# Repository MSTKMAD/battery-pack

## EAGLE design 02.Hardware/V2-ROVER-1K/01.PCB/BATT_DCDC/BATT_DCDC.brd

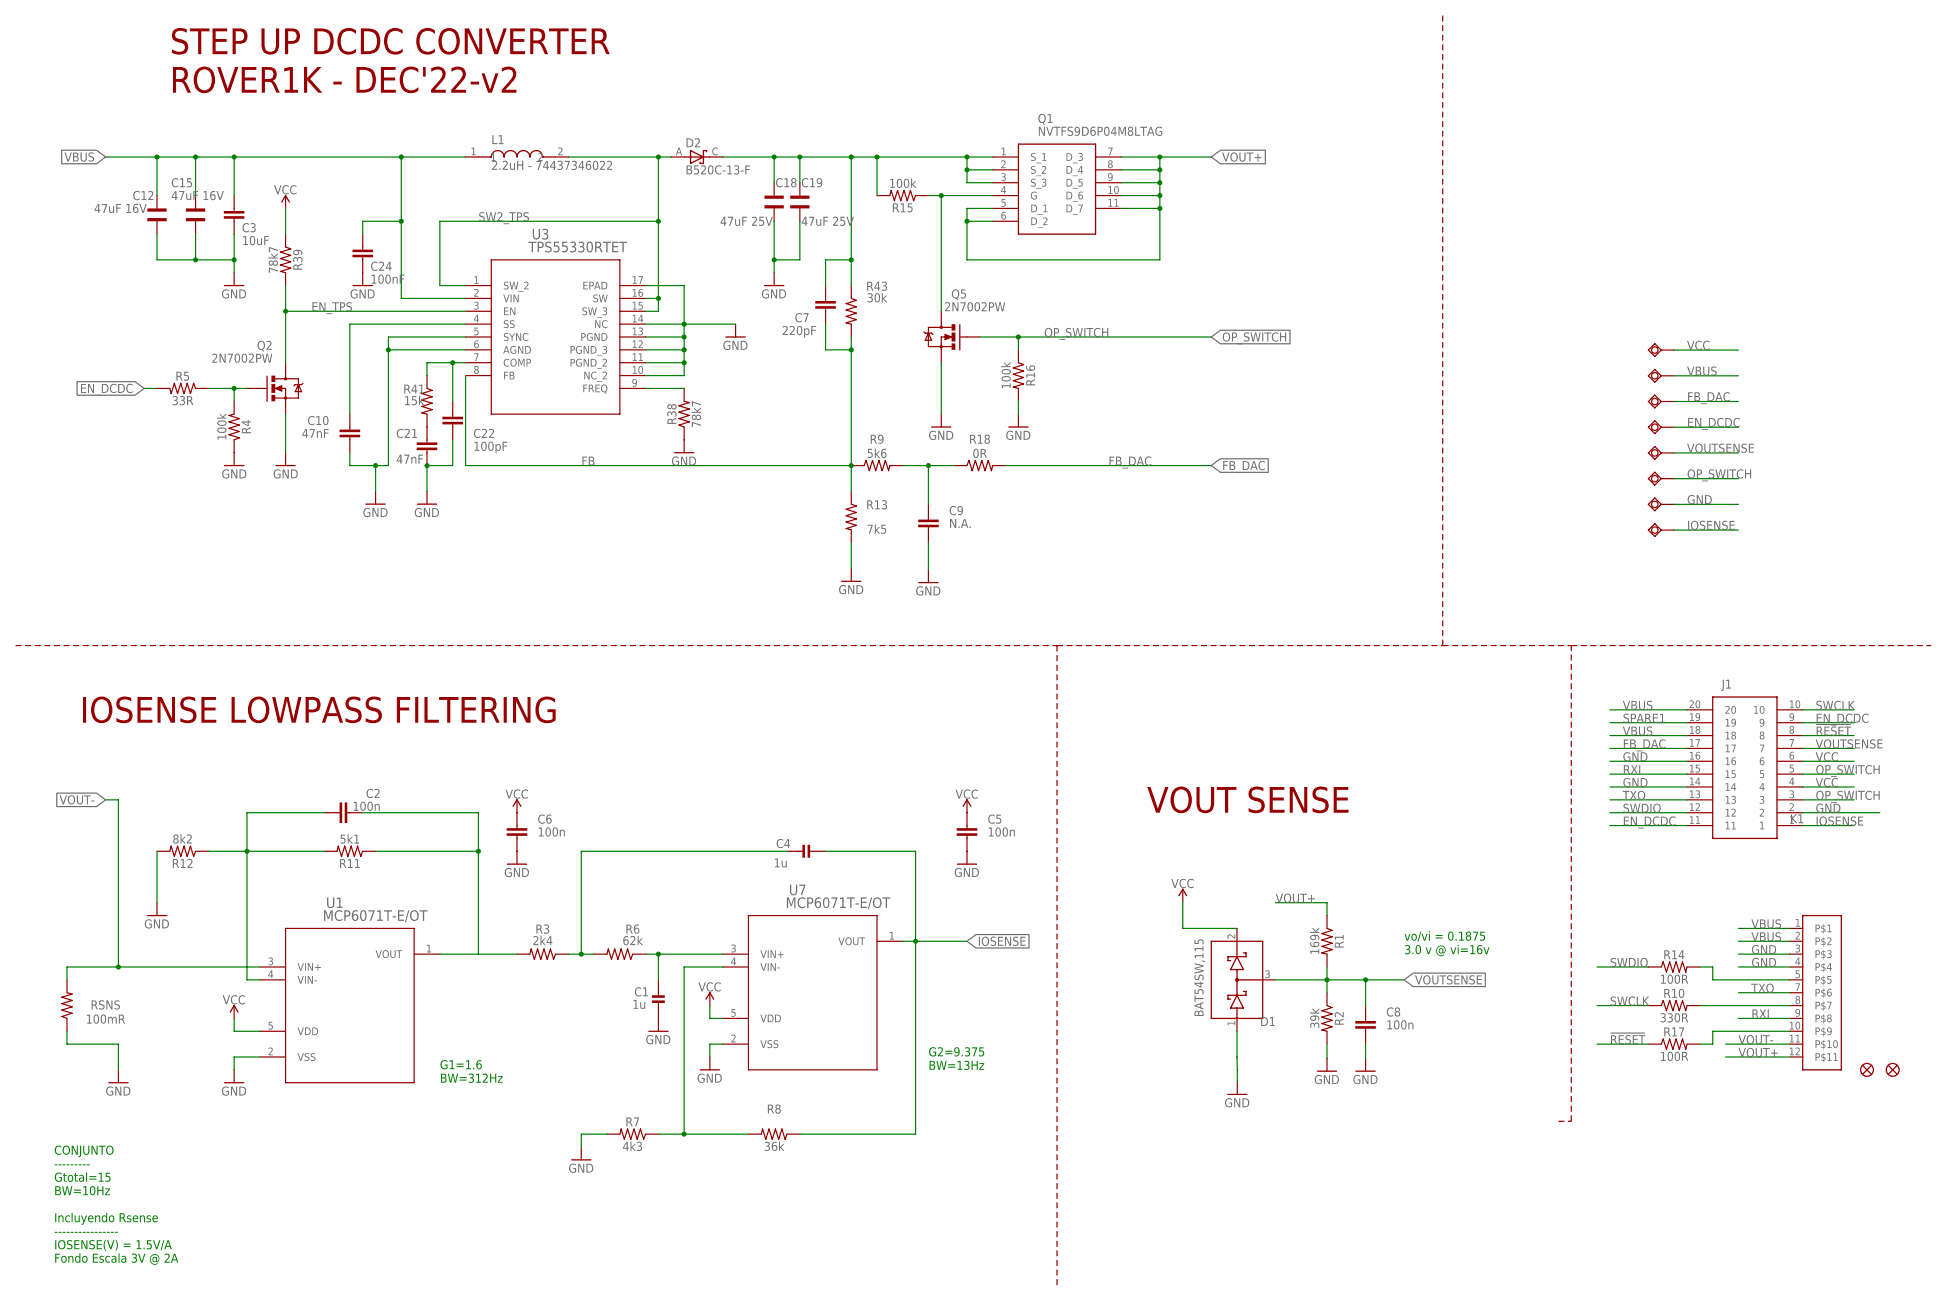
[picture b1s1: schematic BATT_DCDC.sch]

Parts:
C1, C4: 1u; 0603-NO
C2, C5, C6, C8: 100n; 0603
C3: 10uF; 0805
C7: 220pF; 0603
C9: N.A.; 0603
C10, C21: 47nF; 0603
C12, C15: 47uF 16V; WCAP-CSGP_1210
C18, C19: 47uF 25V; WCAP-CSGP_1210
C22: 100pF; 0603
C24: 100nF; 0603
D1: BAT54SW,115; SOT65P210X110-3N
D2: B520C-13-F; DIOM7959X250N
EN_DCDC: TESTPAD_TPSQB1,27; TESTPAD_B1,27
FB_DAC: TESTPAD_TPSQB1,27; TESTPAD_B1,27
GND: TESTPAD_TPSQB1,27; TESTPAD_B1,27
IOSENSE: TESTPAD_TPSQB1,27; TESTPAD_B1,27
J1: DF40C-20DP-0.4V_51_; DF40C-20DPA
K1: FLEX11
L1: 2.2uH - 74437346022; INDM7366X500
OP_SWITCH: TESTPAD_TPSQB1,27; TESTPAD_B1,27
Q1: NVTFS9D6P04M8LTAG; NVTFS5124PLTWG
Q2, Q5: 2N7002PW; SOT323
R1: 169k; 0402
R2: 39k; 0402
R3: 2k4; 0603
R4, R15, R16: 100k; 0402
R5: 33R; 0402
R6: 62k; 0603
R7: 4k3; 0603
R8: 36k; 0603
R9: 5k6; 0402
R10: 330R; 0402
R11: 5k1; 0402
R12: 8k2; 0402
R13: 7k5; 0402
R14, R17: 100R; 0402
R18: 0R; 0402
R38, R39: 78k7; 0402
R41: 15k; 0402
R43: 30k; 0402
RSNS: 100mR; 1206
U1, U7: MCP6071T-E/OT; SOT-23-5_MC_MCH
U3: TPS55330RTET; RTE16_1P66X1P66_TEX
U$1, U$2: FIDUCIAL""; FIDUCIAL_1MM
VBUS: TESTPAD_TPSQB1,27; TESTPAD_B1,27
VCC: TESTPAD_TPSQB1,27; TESTPAD_B1,27
VOUTSENSE: TESTPAD_TPSQB1,27; TESTPAD_B1,27

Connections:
!RESET: J1.8, R17.1
COMP_TPS: C22.2, R41.1, U3.7 (COMP)
EN_DCDC: EN_DCDC.TP, J1.9, J1.11, R5.2
EN_TPS: Q2.3 (D), R39.2, U3.3 (EN)
FB: C7.1, R9.1, R13.1, R43.2, U3.8 (FB)
FB_DAC: FB_DAC.TP, J1.17, R18.2
FREQ_TPS: R38.2, U3.9 (FREQ)
GND: C1.2, C3.1, C5.2, C6.2, C8.2, C9.2, C10.2, C12.1, C15.1, C18.1, C19.1, C21.1, C22.1, C24.1, D1.1 (A), GND.TP, J1.2, J1.14, J1.16, K1.3, K1.4, Q2.2 (S), Q5.2 (S), R2.2, R4.1, R7.2, R12.2, R13.2, R16.2, R38.1, RSNS.1, U1.2 (VSS), U3.5 (SYNC), U3.6 (AGND), U3.10 (NC_2), U3.11 (PGND_2), U3.12 (PGND_3), U3.13 (PGND), U3.14 (NC), U3.17 (EPAD), U7.2 (VSS)
IOSENSE: C4.2, IOSENSE.TP, J1.1, R8.1, U7.1 (VOUT)
ISENSE_RAW: C2.1, R3.2, R11.1, U1.1 (VOUT)
unnamed: C2.2, R11.2, R12.1, U1.4 (VIN-)
unnamed: R7.1, R8.2, U7.4 (VIN-)
unnamed: C4.1, R3.1, R6.2
unnamed: Q2.1 (G), R4.2, R5.1
unnamed: C1.1, R6.1, U7.3 (VIN+)
unnamed: K1.8, R10.2
unnamed: Q1.4 (G), Q5.3 (D), R15.1
unnamed: K1.10, R17.2
unnamed: K1.5, R14.2
unnamed: C9.1, R9.2, R18.1
unnamed: C10.1, U3.4 (SS)
unnamed: C21.2, R41.2
OP_SWITCH: J1.3, J1.5, OP_SWITCH.TP, Q5.1 (G), R16.1
RXI: J1.15, K1.9
SPARE1: J1.19
SW2_TPS: D2.A, L1.2, U3.1 (SW_2), U3.15 (SW_3), U3.16 (SW)
SWCLK: J1.10, R10.1
SWDIO: J1.12, R14.1
TXO: J1.13, K1.7
VBUS: C3.2, C12.2, C15.2, C24.2, J1.18, J1.20, K1.1, K1.2, L1.1, U3.2 (VIN), VBUS.TP
VCC: C5.1, C6.1, D1.2 (C), J1.4, J1.6, R39.1, U1.5 (VDD), U7.5 (VDD), VCC.TP
VOUT+: K1.12, Q1.5 (D_1), Q1.6 (D_2), Q1.7 (D_3), Q1.8 (D_4), Q1.9 (D_5), Q1.10 (D_6), Q1.11 (D_7), R1.1
VOUT-: K1.11, RSNS.2, U1.3 (VIN+)
VOUTSENSE: C8.1, D1.3 (A-C), J1.7, R1.2, R2.1, VOUTSENSE.TP
VSOURCE: C7.2, C18.2, C19.2, D2.C, Q1.1 (S_1), Q1.2 (S_2), Q1.3 (S_3), R15.2, R43.1

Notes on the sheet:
vo/vi = 0.1875 3.0 v @ vi=16v
VOUT SENSE
G2=9.375 BW=13Hz
IOSENSE LOWPASS FILTERING
STEP UP DCDC CONVERTER ROVER1K - DEC'22-v2
G1=1.6 BW=312Hz
CONJUNTO --------- Gtotal=15 BW=10Hz Incluyendo Rsense ---------------- IOSENSE(V) = 1.5V/A Fondo Escala 3V @ 2A

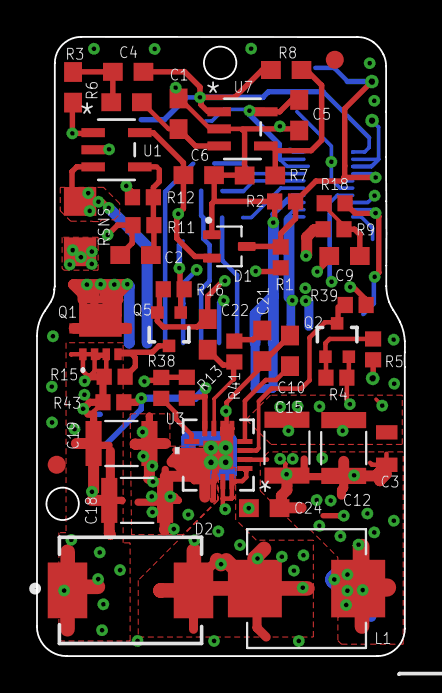
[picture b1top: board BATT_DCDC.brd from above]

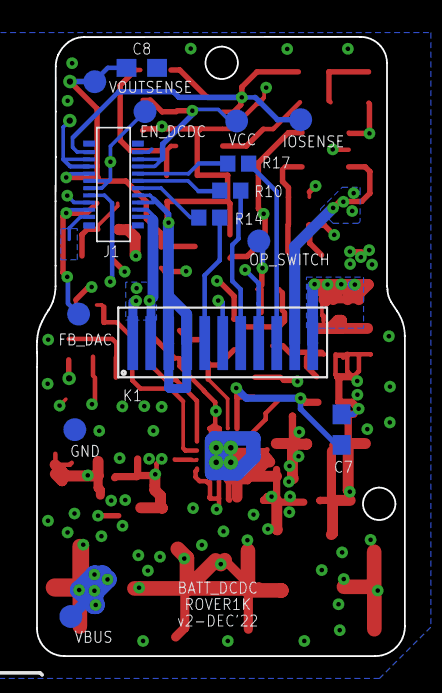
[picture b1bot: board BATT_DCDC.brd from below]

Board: 4 copper layers, 20.4 x 34.4 mm, 61 parts (15 on the bottom side), 34 nets.

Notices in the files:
parts and their libraries:
microbuilder: This work is placed in the public domain, and may be freely used for commercial and non-commercial work with the following conditions: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
SparkFun-Resistors: Licensing: Creative Commons ShareAlike 4.0 International - https://creativecommons.org/licenses/by-sa/4.0
